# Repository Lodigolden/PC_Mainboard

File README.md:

# PC_Mainboard
The hardware for a mainboard for the personal computer.

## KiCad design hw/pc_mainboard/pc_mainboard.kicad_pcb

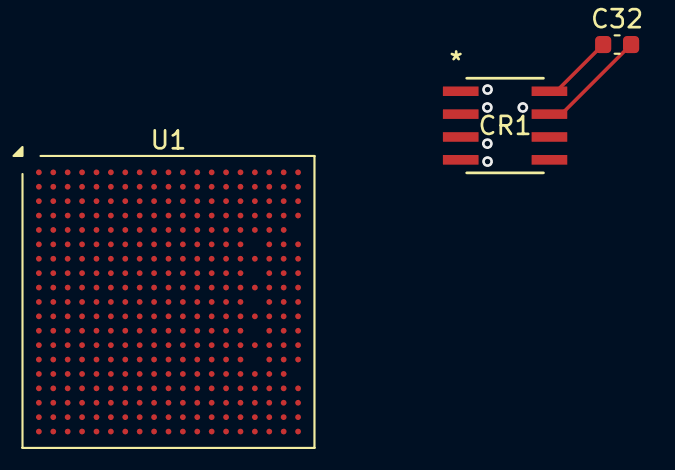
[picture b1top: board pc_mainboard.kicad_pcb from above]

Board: 2 copper layers, 3 parts (0 on the bottom side), 5 nets.

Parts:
C32: 100n; C_0603_1608Metric
CR1: eeprom_M24C02-WMN6TP; eeprom_SO-8_STM
U1: STM32MP151AABx; ST_LFBGA-354_16x16mm_Layout19x19_P0.8mm

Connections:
+3V3: C32.1, CR1.8 (VCC)
GND: C32.2, CR1.1 (E0), CR1.2 (E1), CR1.3 (E2), CR1.4 (VSS), CR1.7 (*WC)
unnamed: U1.A1 (VSS), U1.A19 (VSS), U1.B2 (VSS), U1.B6 (VSS), U1.C3 (VSS), U1.C12 (VSS), U1.C13 (VSS), U1.C14 (VSS), U1.C15 (VSS), U1.C16 (VSS), U1.C17 (VSS), U1.D1 (VSS), U1.D4 (VSS), U1.D5 (VSS), U1.D8 (VSS), U1.E2 (VSS), U1.E4 (VSS), U1.E5 (VSS), U1.E6 (VSS), U1.E8 (VSS), U1.E10 (VSS), U1.E12 (VSS), U1.E14 (VSS), U1.E16 (VSS), U1.F5 (VSS), U1.F7 (VSS), U1.F9 (VSS), U1.F11 (VSS), U1.F15 (VSS), U1.G2 (VSS), U1.G4 (VSS), U1.G6 (VSS), U1.G8 (VSS), U1.G10 (VSS), U1.G12 (VSS), U1.G14 (VSS), U1.H5 (VSS), U1.H7 (VSS), U1.H9 (VSS), U1.H11 (VSS), U1.H13 (VSS), U1.H15 (VSS), U1.J3 (VSS), U1.J6 (VSS), U1.J8 (VSS), U1.J10 (VSS), U1.J12 (VSS), U1.J14 (VSS), U1.K2 (VSS), U1.K5 (VSS), U1.K7 (VSS), U1.K9 (VSS), U1.K11 (VSS), U1.K13 (VSS), U1.K15 (VSS), U1.L6 (VSS), U1.L8 (VSS), U1.L10 (VSS), U1.L12 (VSS), U1.L14 (VSS), U1.M5 (VSS), U1.M7 (VSS), U1.M9 (VSS), U1.M11 (VSS), U1.M13 (VSS), U1.M15 (VSS), U1.N6 (VSS), U1.N8 (VSS), U1.N10 (VSS), U1.N12 (VSS), U1.N14 (VSS), U1.P7 (VSS), U1.P9 (VSS), U1.P11 (VSS), U1.P13 (VSS), U1.P15 (VSS), U1.R2 (VSS), U1.R6 (VSS), U1.R8 (VSS), U1.R10 (VSS), U1.R12 (VSS), U1.R14 (VSS), U1.R16 (VSS), U1.T4 (VSS), U1.U3 (VSS), U1.U6 (VSS), U1.U8 (VSS), U1.U17 (VSS), U1.W1 (VSS), U1.W19 (VSS)
unnamed: U1.N4 (VSSA), U1.P5 (VSSA), U1.R5 (VSSA)
unnamed: U1.U13 (VSS_USBHS), U1.U14 (VSS_USBHS), U1.V12 (VSS_USBHS), U1.V15 (VSS_USBHS)

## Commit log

2025-08-30 Initial repo setup
2025-08-30 Added CODEOWNERS file
2025-08-30 Initial repo setup (#2)
    * Initial repo setup
2025-08-31 System block diagram
2025-08-31 System block diagram (#6)
2025-08-31 Added MPU information
2025-08-31 Added MPU information (#9)
2025-08-31 Added RAM information
2025-08-31 Added RAM information (#10)
2025-08-31 Added PHY research
2025-08-31 Added PHY research (#13)
2025-08-31 Research for serial interface
2025-08-31 Research for serial interface (#15)
2025-08-31 Added RTC
2025-08-31 Added RTC (#22)
2025-08-31 Added serial schematic capture
2025-08-31 Added serial schematic capture (#34)
2025-09-01 RTC Schematic Capture
2025-09-01 RTC Schematic Capture (#35)
2025-09-01 EEPROM Research
2025-09-01 EEPROM Research (#36)
2025-09-01 Watchdog research
2025-09-01 Watchdog research (#37)
2025-09-01 Watchdog schematic capture
2025-09-01 Watchdog schematic capture (#38)
2025-09-02 RAM Schematic Capture
2025-09-02 RAM Schematic Capture (#39)
2025-09-06 eeprom schematic, partial layout
2025-09-06 eeprom schematic, partial layout (#40)
2025-09-06 Added I2C address table
2025-09-06 Added Konnor to CODEOWNERS file
2025-09-06 cleanup eeprom schematic format: removed crossed wires and localized endpoints
2025-09-06 HDMI transmitter research
2025-09-09 Added I2C address table (#43)
    * Added I2C address table
    * Added Konnor to CODEOWNERS file
2025-09-09 SD card research, updated some formatting
2025-09-10 SD card research, updated some formatting (#49)
2025-09-13 v1 HDMI Transmitter Schematic
2025-10-01 Flash research
2025-10-01 Flash research (#53)
2025-10-01 Schematic capture Flash
2025-10-01 Schematic capture Flash (#54)
